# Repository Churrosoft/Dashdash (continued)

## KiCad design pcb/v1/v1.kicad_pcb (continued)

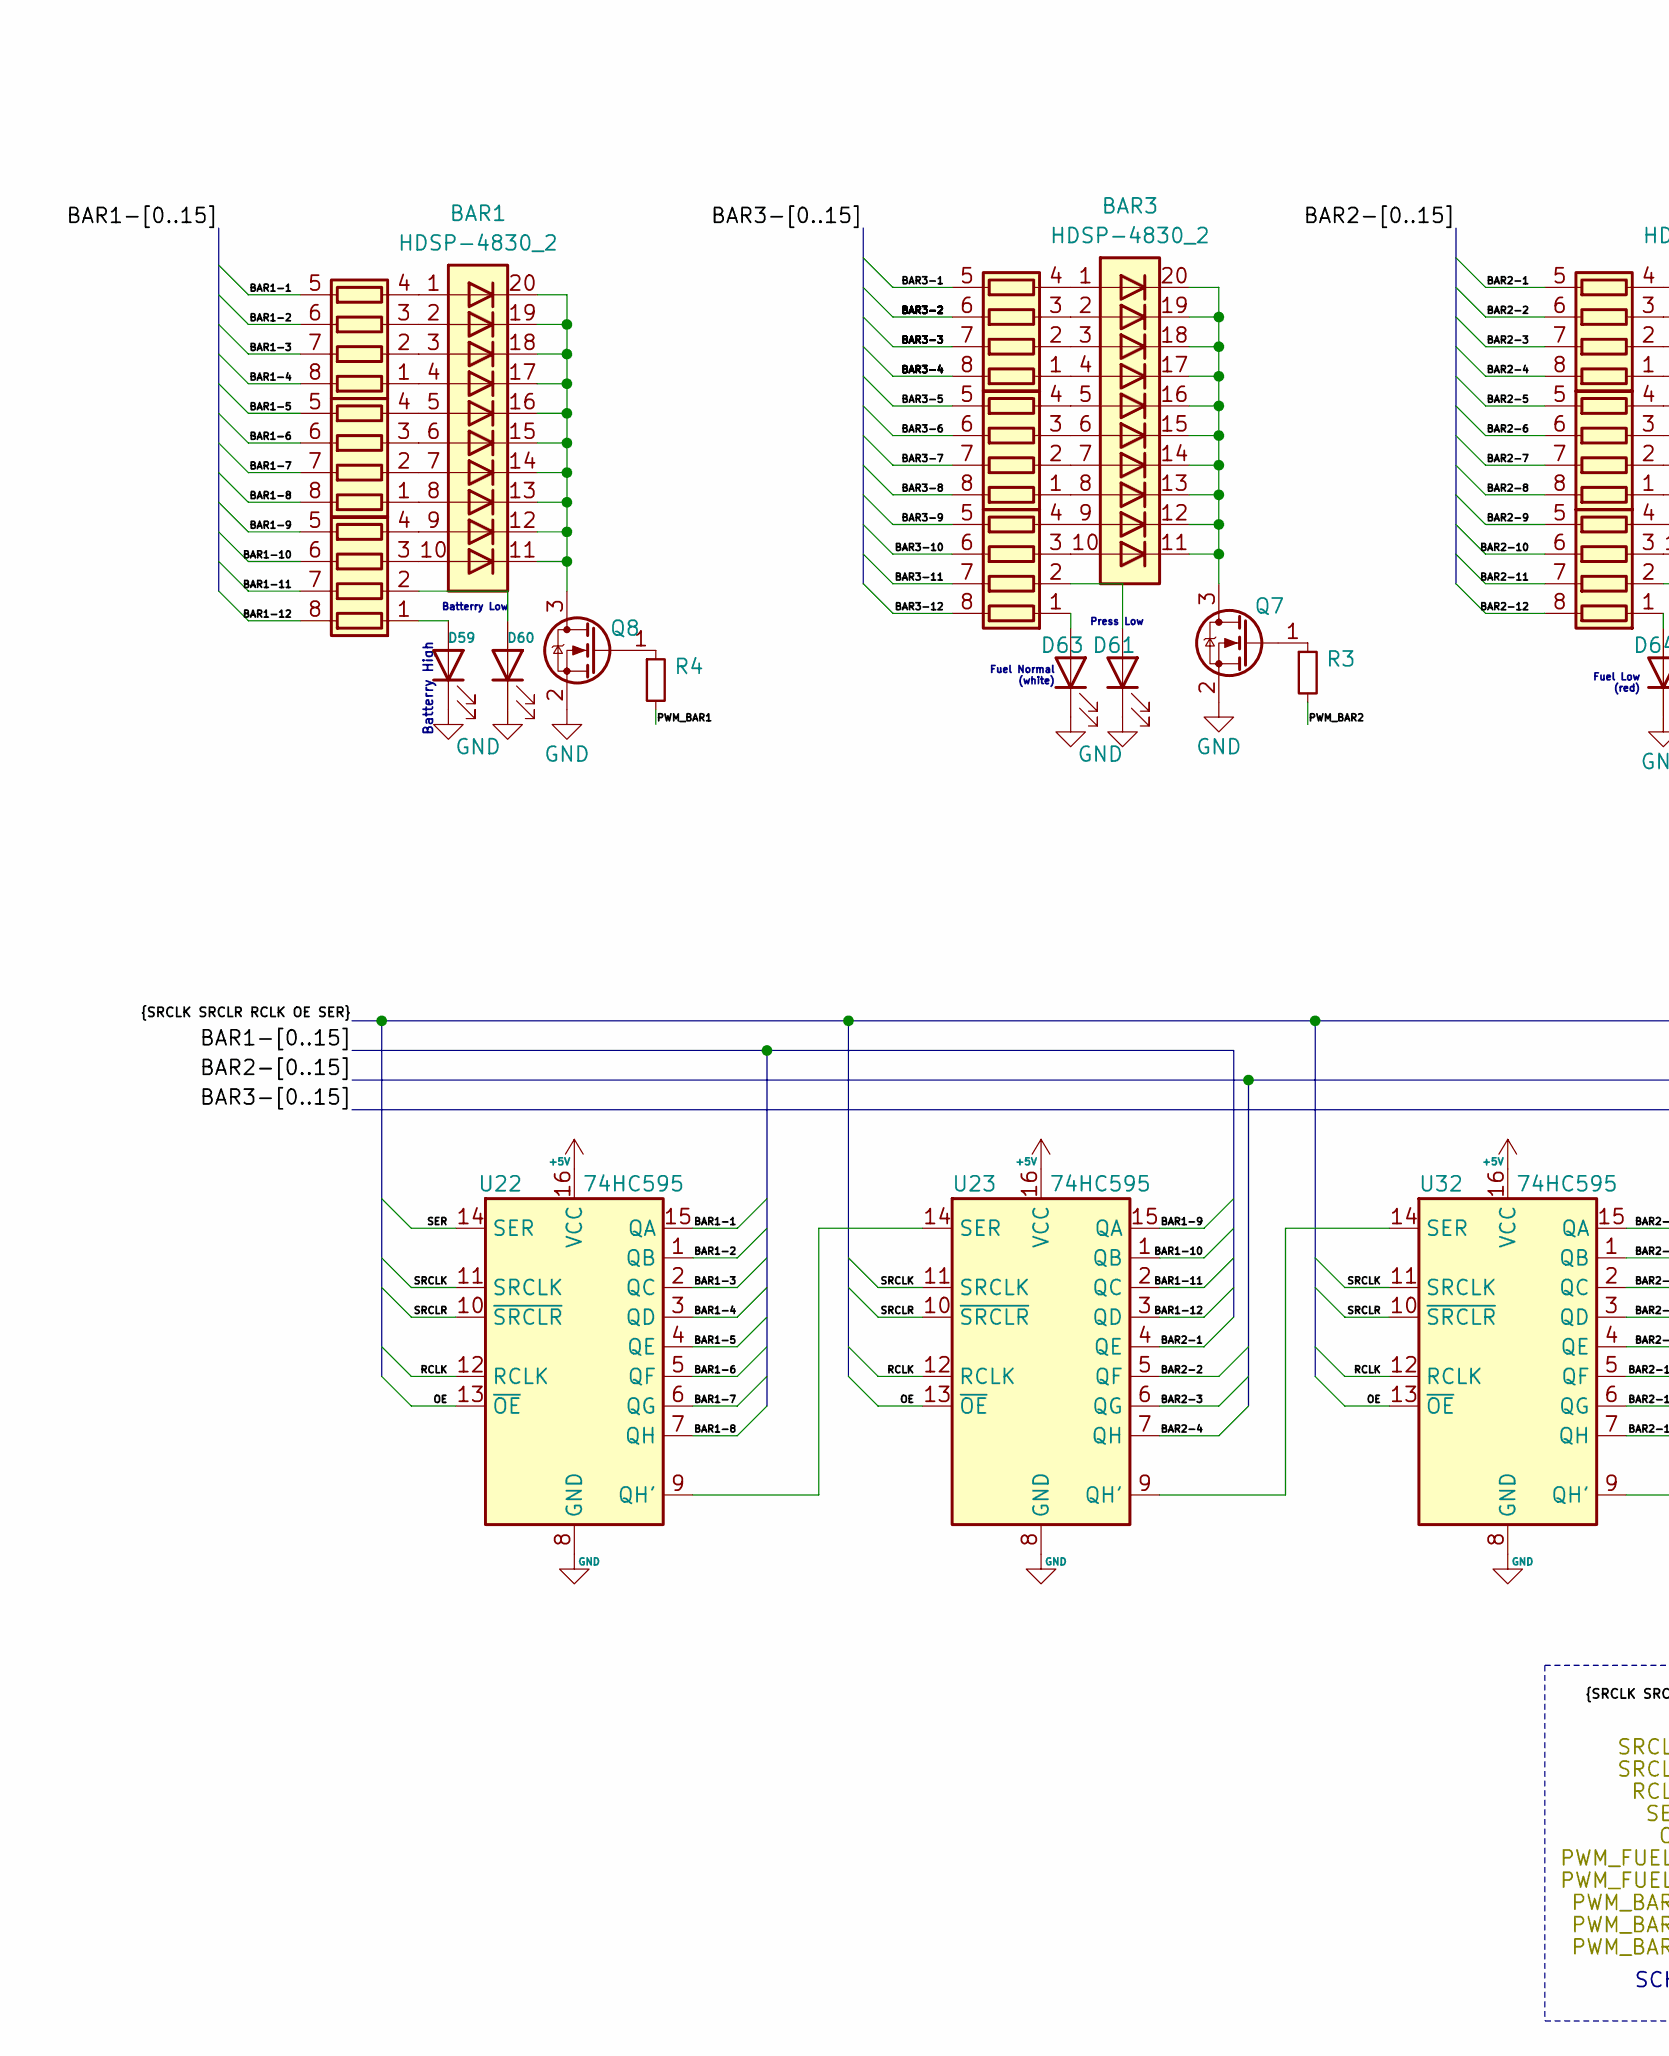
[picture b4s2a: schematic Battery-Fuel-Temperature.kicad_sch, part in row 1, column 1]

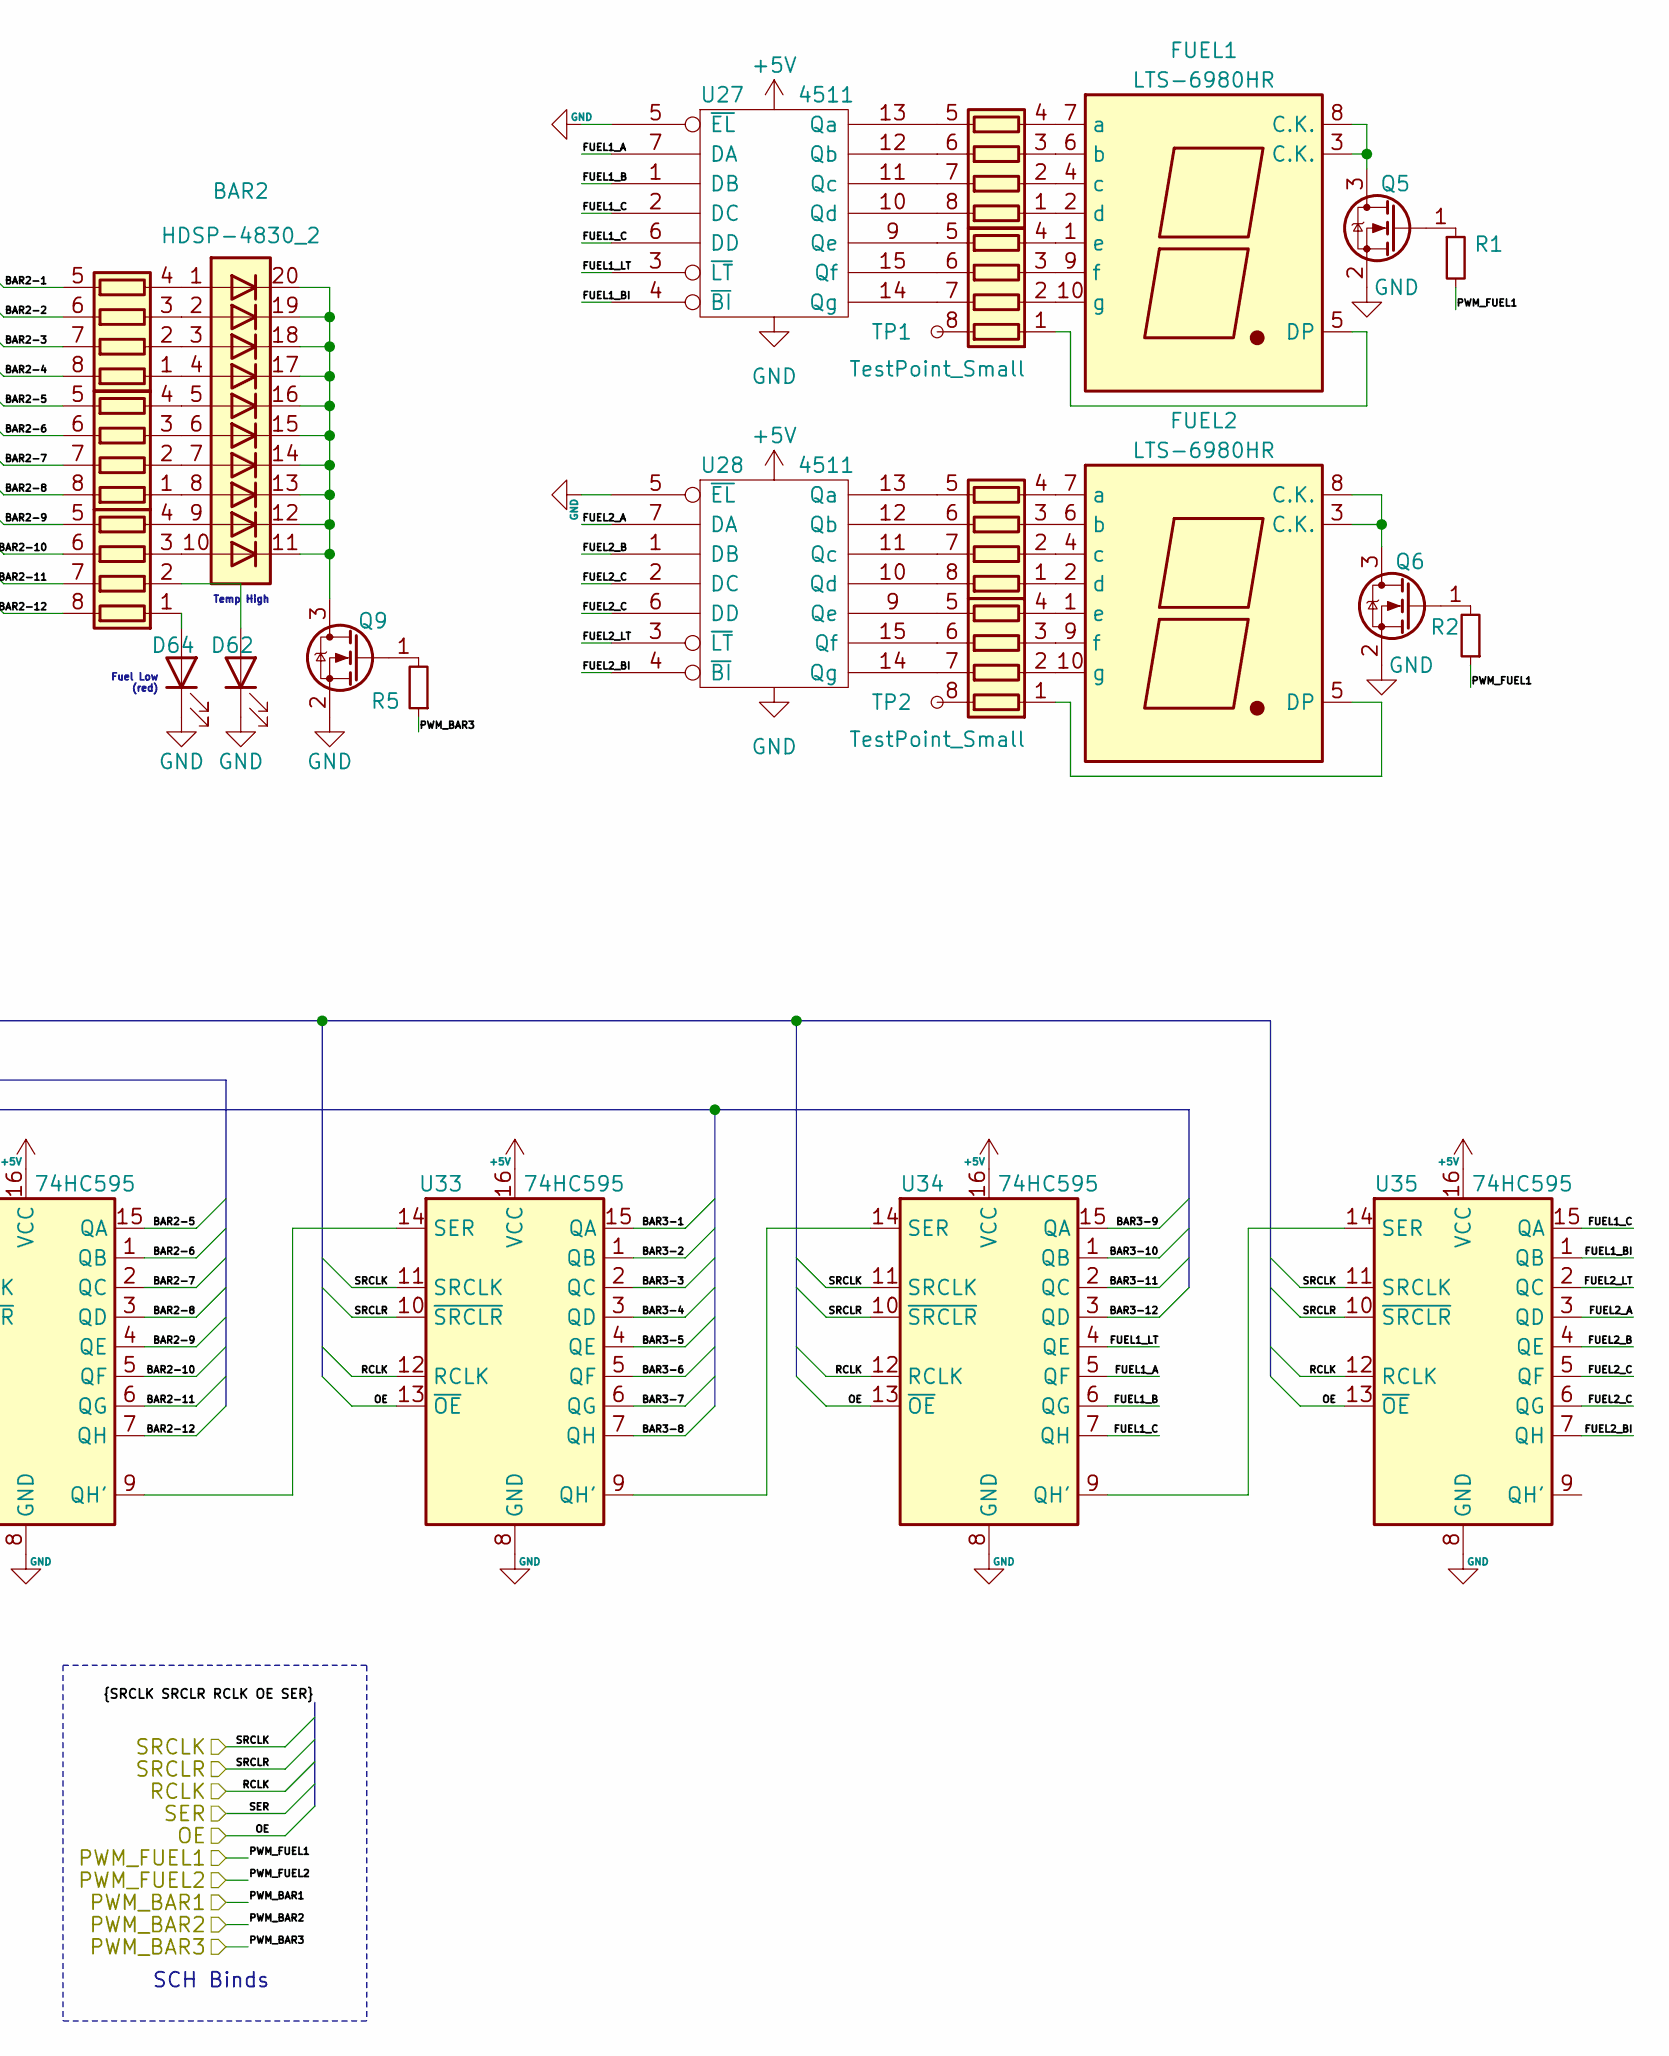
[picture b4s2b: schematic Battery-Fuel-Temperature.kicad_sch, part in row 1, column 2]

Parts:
BAR1, BAR2, BAR3: HDSP-4830_2; HDSP-4830
D59, D60, D61, D62, D63, D64: LED; LED_0805_2012Metric_Castellated; LCSC C205447
FUEL1, FUEL2: LTS-6980HR; 7SegmentLED_LTS6760_LTS6780
Q5, Q6, Q7, Q8, Q9: BSS138; SOT-23
R1, R2, R3, R4, R5: 1k 1/10W +-1%; R_0603_1608Metric; LCSC C217840
RN13, RN14, RN15, RN16, RN17, RN18, RN19, RN20, RN21, RN22, RN23, RN24, RN25: 560Ω ±5% 63mW; R_Array_Convex_4x0603; LCSC C253481
TP1, TP2: TestPoint_Small; TestPoint_Pad_1.0x1.0mm
U22, U23, U32, U33, U34, U35: 74HC595; TSSOP-16_4.4x5mm_P0.65mm; LCSC C5948
U27, U28: 4511; TSSOP-16_4.4x5mm_P0.65mm; LCSC C356693

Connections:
/BFT_OE_L: U22.12 (RCLK), U23.12 (RCLK), U32.12 (RCLK), U33.12 (RCLK), U34.12 (RCLK), U35.12 (RCLK)
/BFT_RCLK_L: U22.10 (~SRCLR), U23.10 (~SRCLR), U32.10 (~SRCLR), U33.10 (~SRCLR), U34.10 (~SRCLR), U35.10 (~SRCLR)
/BFT_SER_L: U22.14 (SER)
/BFT_SRCLK_L: U22.13 (~OE), U23.13 (~OE), U32.13 (~OE), U33.13 (~OE), U34.13 (~OE), U35.13 (~OE)
/BFT_SRCLR_L: U22.11 (SRCLK), U23.11 (SRCLK), U32.11 (SRCLK), U33.11 (SRCLK), U34.11 (SRCLK), U35.11 (SRCLK)
/Battery/Fuel/Temperature indicators/BAR1-1: RN13.5 (R4.2), U22.15 (QA)
/Battery/Fuel/Temperature indicators/BAR1-2: RN13.6 (R3.2), U22.1 (QB)
/Battery/Fuel/Temperature indicators/BAR1-3: RN13.7 (R2.2), U22.2 (QC)
/Battery/Fuel/Temperature indicators/BAR1-4: RN13.8 (R1.2), U22.3 (QD)
/Battery/Fuel/Temperature indicators/BAR1-5: RN16.5 (R4.2), U22.4 (QE)
/Battery/Fuel/Temperature indicators/BAR1-6: RN16.6 (R3.2), U22.5 (QF)
/Battery/Fuel/Temperature indicators/BAR1-7: RN16.7 (R2.2), U22.6 (QG)
/Battery/Fuel/Temperature indicators/BAR1-8: RN16.8 (R1.2), U22.7 (QH)
/Battery/Fuel/Temperature indicators/BAR1-9: RN21.5 (R4.2), U23.15 (QA)
/Battery/Fuel/Temperature indicators/BAR1-10: RN21.6 (R3.2), U23.1 (QB)
/Battery/Fuel/Temperature indicators/BAR1-11: RN21.7 (R2.2), U23.2 (QC)
/Battery/Fuel/Temperature indicators/BAR1-12: RN21.8 (R1.2), U23.3 (QD)
/Battery/Fuel/Temperature indicators/BAR2-1: RN15.5 (R4.2), U23.4 (QE)
/Battery/Fuel/Temperature indicators/BAR2-2: RN15.6 (R3.2), U23.5 (QF)
/Battery/Fuel/Temperature indicators/BAR2-3: RN15.7 (R2.2), U23.6 (QG)
/Battery/Fuel/Temperature indicators/BAR2-4: RN15.8 (R1.2), U23.7 (QH)
/Battery/Fuel/Temperature indicators/BAR2-5: RN20.5 (R4.2), U32.15 (QA)
/Battery/Fuel/Temperature indicators/BAR2-6: RN20.6 (R3.2), U32.1 (QB)
/Battery/Fuel/Temperature indicators/BAR2-7: RN20.7 (R2.2), U32.2 (QC)
/Battery/Fuel/Temperature indicators/BAR2-8: RN20.8 (R1.2), U32.3 (QD)
/Battery/Fuel/Temperature indicators/BAR2-9: RN25.5 (R4.2), U32.4 (QE)
/Battery/Fuel/Temperature indicators/BAR2-10: RN25.6 (R3.2), U32.5 (QF)
/Battery/Fuel/Temperature indicators/BAR2-11: RN25.7 (R2.2), U32.6 (QG)
/Battery/Fuel/Temperature indicators/BAR2-12: RN25.8 (R1.2), U32.7 (QH)
/Battery/Fuel/Temperature indicators/BAR3-1: RN14.5 (R4.2), U33.15 (QA)
/Battery/Fuel/Temperature indicators/BAR3-2: RN14.6 (R3.2), U33.1 (QB)
/Battery/Fuel/Temperature indicators/BAR3-3: RN14.7 (R2.2), U33.2 (QC)
/Battery/Fuel/Temperature indicators/BAR3-4: RN14.8 (R1.2), U33.3 (QD)
/Battery/Fuel/Temperature indicators/BAR3-5: RN17.5 (R4.2), U33.4 (QE)
/Battery/Fuel/Temperature indicators/BAR3-6: RN17.6 (R3.2), U33.5 (QF)
/Battery/Fuel/Temperature indicators/BAR3-7: RN17.7 (R2.2), U33.6 (QG)
/Battery/Fuel/Temperature indicators/BAR3-8: RN17.8 (R1.2), U33.7 (QH)
/Battery/Fuel/Temperature indicators/BAR3-9: RN22.5 (R4.2), U34.15 (QA)
/Battery/Fuel/Temperature indicators/BAR3-10: RN22.6 (R3.2), U34.1 (QB)
/Battery/Fuel/Temperature indicators/BAR3-11: RN22.7 (R2.2), U34.2 (QC)
/Battery/Fuel/Temperature indicators/BAR3-12: RN22.8 (R1.2), U34.3 (QD)
/Battery/Fuel/Temperature indicators/FUEL1_A: U27.7 (DA), U34.5 (QF)
/Battery/Fuel/Temperature indicators/FUEL1_B: U27.1 (DB), U34.6 (QG)
/Battery/Fuel/Temperature indicators/FUEL1_BI: U27.4 (~BI), U35.1 (QB)
/Battery/Fuel/Temperature indicators/FUEL1_C: U27.2 (DC), U27.6 (DD), U34.7 (QH), U35.15 (QA)
/Battery/Fuel/Temperature indicators/FUEL1_LT: U27.3 (~LT), U34.4 (QE)
/Battery/Fuel/Temperature indicators/FUEL2_A: U28.7 (DA), U35.3 (QD)
/Battery/Fuel/Temperature indicators/FUEL2_B: U28.1 (DB), U35.4 (QE)
/Battery/Fuel/Temperature indicators/FUEL2_BI: U28.4 (~BI), U35.7 (QH)
/Battery/Fuel/Temperature indicators/FUEL2_C: U28.2 (DC), U28.6 (DD), U35.5 (QF), U35.6 (QG)
/Battery/Fuel/Temperature indicators/FUEL2_LT: U28.3 (~LT), U35.2 (QC)
/PWM_BAR1: R4.2; also elsewhere on the board
/PWM_BAR2: R3.2; also elsewhere on the board
/PWM_BAR3: R5.1; also elsewhere on the board
/PWM_FUEL1: R1.2, R2.1; also elsewhere on the board
GND: D59.1 (K), D60.1 (K), D61.1 (K), D62.1 (K), D63.1 (K), D64.1 (K), Q5.2 (S), Q6.2 (S), Q7.2 (S), Q8.2 (S), Q9.2 (S), U22.8 (GND), U23.8 (GND), U27.5 (~EL), U27.8 (Vss), U28.5 (~EL), U28.8 (Vss), U32.8 (GND), U33.8 (GND), U34.8 (GND), U35.8 (GND); also elsewhere on the board
unnamed: BAR1.1 (A), RN13.4 (R4.1)
unnamed: BAR1.2 (A), RN13.3 (R3.1)
unnamed: BAR1.3 (A), RN13.2 (R2.1)
unnamed: BAR1.4 (A), RN13.1 (R1.1)
unnamed: BAR1.5 (A), RN16.4 (R4.1)
unnamed: BAR1.6 (A), RN16.3 (R3.1)
unnamed: BAR1.7 (A), RN16.2 (R2.1)
unnamed: BAR1.8 (A), RN16.1 (R1.1)
unnamed: BAR1.9 (A), RN21.4 (R4.1)
unnamed: BAR1.10 (A), RN21.3 (R3.1)
unnamed: BAR1.11 (K), BAR1.12 (K), BAR1.13 (K), BAR1.14 (K), BAR1.15 (K), BAR1.16 (K), BAR1.17 (K), BAR1.18 (K), BAR1.19 (K), BAR1.20 (K), Q8.3 (D)
unnamed: BAR2.1 (A), RN15.4 (R4.1)
unnamed: BAR2.2 (A), RN15.3 (R3.1)
unnamed: BAR2.3 (A), RN15.2 (R2.1)
unnamed: BAR2.4 (A), RN15.1 (R1.1)
unnamed: BAR2.5 (A), RN20.4 (R4.1)
unnamed: BAR2.6 (A), RN20.3 (R3.1)
unnamed: BAR2.7 (A), RN20.2 (R2.1)
unnamed: BAR2.8 (A), RN20.1 (R1.1)
unnamed: BAR2.9 (A), RN25.4 (R4.1)
unnamed: BAR2.10 (A), RN25.3 (R3.1)
unnamed: BAR2.11 (K), BAR2.12 (K), BAR2.13 (K), BAR2.14 (K), BAR2.15 (K), BAR2.16 (K), BAR2.17 (K), BAR2.18 (K), BAR2.19 (K), BAR2.20 (K), Q9.3 (D)
unnamed: BAR3.1 (A), RN14.4 (R4.1)
unnamed: BAR3.2 (A), RN14.3 (R3.1)
unnamed: BAR3.3 (A), RN14.2 (R2.1)
unnamed: BAR3.4 (A), RN14.1 (R1.1)
unnamed: BAR3.5 (A), RN17.4 (R4.1)
unnamed: BAR3.6 (A), RN17.3 (R3.1)
unnamed: BAR3.7 (A), RN17.2 (R2.1)
unnamed: BAR3.8 (A), RN17.1 (R1.1)
unnamed: BAR3.9 (A), RN22.4 (R4.1)
unnamed: BAR3.10 (A), RN22.3 (R3.1)
unnamed: BAR3.11 (K), BAR3.12 (K), BAR3.13 (K), BAR3.14 (K), BAR3.15 (K), BAR3.16 (K), BAR3.17 (K), BAR3.18 (K), BAR3.19 (K), BAR3.20 (K), Q7.3 (D)
unnamed: D59.2 (A), RN21.1 (R1.1)
unnamed: D60.2 (A), RN21.2 (R2.1)
unnamed: D61.2 (A), RN22.2 (R2.1)
unnamed: D62.2 (A), RN25.2 (R2.1)
unnamed: D63.2 (A), RN22.1 (R1.1)
unnamed: D64.2 (A), RN25.1 (R1.1)
unnamed: FUEL1.1 (e), RN23.4 (R4.1)
unnamed: FUEL1.2 (d), RN18.1 (R1.1)
unnamed: FUEL1.3 (C.K.), FUEL1.8 (C.K.), Q5.3 (D)
unnamed: FUEL1.4 (c), RN18.2 (R2.1)
unnamed: FUEL1.5 (DP), RN23.1 (R1.1)
unnamed: FUEL1.6 (b), RN18.3 (R3.1)
unnamed: FUEL1.7 (a), RN18.4 (R4.1)
unnamed: FUEL1.9 (f), RN23.3 (R3.1)
unnamed: FUEL1.10 (g), RN23.2 (R2.1)
unnamed: FUEL2.1 (e), RN24.4 (R4.1)
unnamed: FUEL2.2 (d), RN19.1 (R1.1)
unnamed: FUEL2.3 (C.K.), FUEL2.8 (C.K.), Q6.3 (D)
unnamed: FUEL2.4 (c), RN19.2 (R2.1)
unnamed: FUEL2.5 (DP), RN24.1 (R1.1)
unnamed: FUEL2.6 (b), RN19.3 (R3.1)
unnamed: FUEL2.7 (a), RN19.4 (R4.1)
unnamed: FUEL2.9 (f), RN24.3 (R3.1)
unnamed: FUEL2.10 (g), RN24.2 (R2.1)
unnamed: Q5.1 (G), R1.1
unnamed: Q6.1 (G), R2.2
unnamed: Q7.1 (G), R3.1
unnamed: Q8.1 (G), R4.1
unnamed: Q9.1 (G), R5.2
unnamed: RN18.5 (R4.2), U27.13 (Qa)
unnamed: RN18.6 (R3.2), U27.12 (Qb)
unnamed: RN18.7 (R2.2), U27.11 (Qc)
unnamed: RN18.8 (R1.2), U27.10 (Qd)
unnamed: RN19.5 (R4.2), U28.13 (Qa)
unnamed: RN19.6 (R3.2), U28.12 (Qb)
unnamed: RN19.7 (R2.2), U28.11 (Qc)
unnamed: RN19.8 (R1.2), U28.10 (Qd)
unnamed: RN23.5 (R4.2), U27.9 (Qe)
unnamed: RN23.6 (R3.2), U27.15 (Qf)
unnamed: RN23.7 (R2.2), U27.14 (Qg)
unnamed: RN23.8 (R1.2), TP1.1
unnamed: RN24.5 (R4.2), U28.9 (Qe)
unnamed: RN24.6 (R3.2), U28.15 (Qf)
unnamed: RN24.7 (R2.2), U28.14 (Qg)
unnamed: RN24.8 (R1.2), TP2.1
unnamed: U22.9 (QH'), U23.14 (SER)
unnamed: U23.9 (QH'), U32.14 (SER)
unnamed: U32.9 (QH'), U33.14 (SER)
unnamed: U33.9 (QH'), U34.14 (SER)
unnamed: U34.9 (QH'), U35.14 (SER)

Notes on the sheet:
Batterry High
Batterry Low
Fuel Normal (white)
Press Low
Fuel Low (red)
Temp High
SCH Binds
